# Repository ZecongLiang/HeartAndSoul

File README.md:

# HeartAndSoul
This is the repository for my smart watch named Heat&amp;Soul.

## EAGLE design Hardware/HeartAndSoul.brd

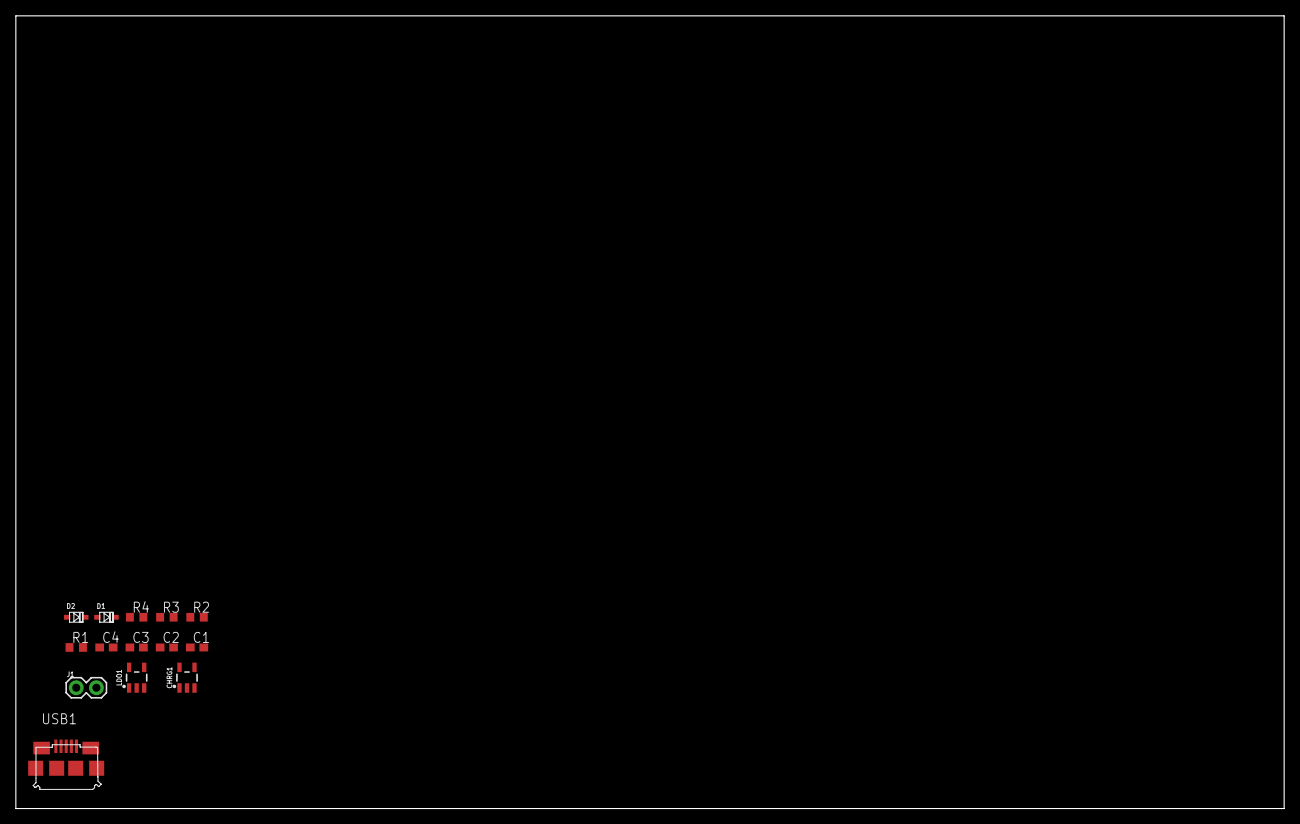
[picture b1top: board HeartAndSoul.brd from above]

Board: 2 copper layers, 160.0 x 100.0 mm, 14 parts (0 on the bottom side), 8 nets, no tracks yet.

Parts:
C1, C2, C3, C4: C0603
CHRG1: MCP73831; SOT23-5
D1, D2: USC
J1: 1X02
LDO1: MIC5504; SOT23-5
R1, R2, R3, R4: R0603
USB1: USB.MICRO-BIGGERPADS; USB-MICRO-01.BIGGERPADS

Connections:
3.3V: C2.1, LDO1.5
BATT: R3.2, R4.1
CHRG.STAT: C3.1, C4.1, CHRG1.4, D1.-, D2.-, LDO1.1, LDO1.3, R2.2
GND: C1.2, C2.2, C3.2, C4.2, J1.1, LDO1.2, R1.2, R4.2, USB1.5
unnamed: CHRG1.1, R2.1
unnamed: CHRG1.5, R1.1
VLIPO: C1.1, CHRG1.3, D1.+, J1.2, R3.1
V_USB: D2.+, USB1.1

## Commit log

2020-09-30 This is a complete revision of smartwatch development
2020-09-30 Complete rev of smartwatch development
2020-09-30 Added TMP36 sensor
2020-09-30 Added existing schematics for components
2020-09-30 Added test code for sensors
2020-09-30 Added temp sensor test code
2020-09-30 Incorporated getTemp() function
2020-09-30 Added temp test code
